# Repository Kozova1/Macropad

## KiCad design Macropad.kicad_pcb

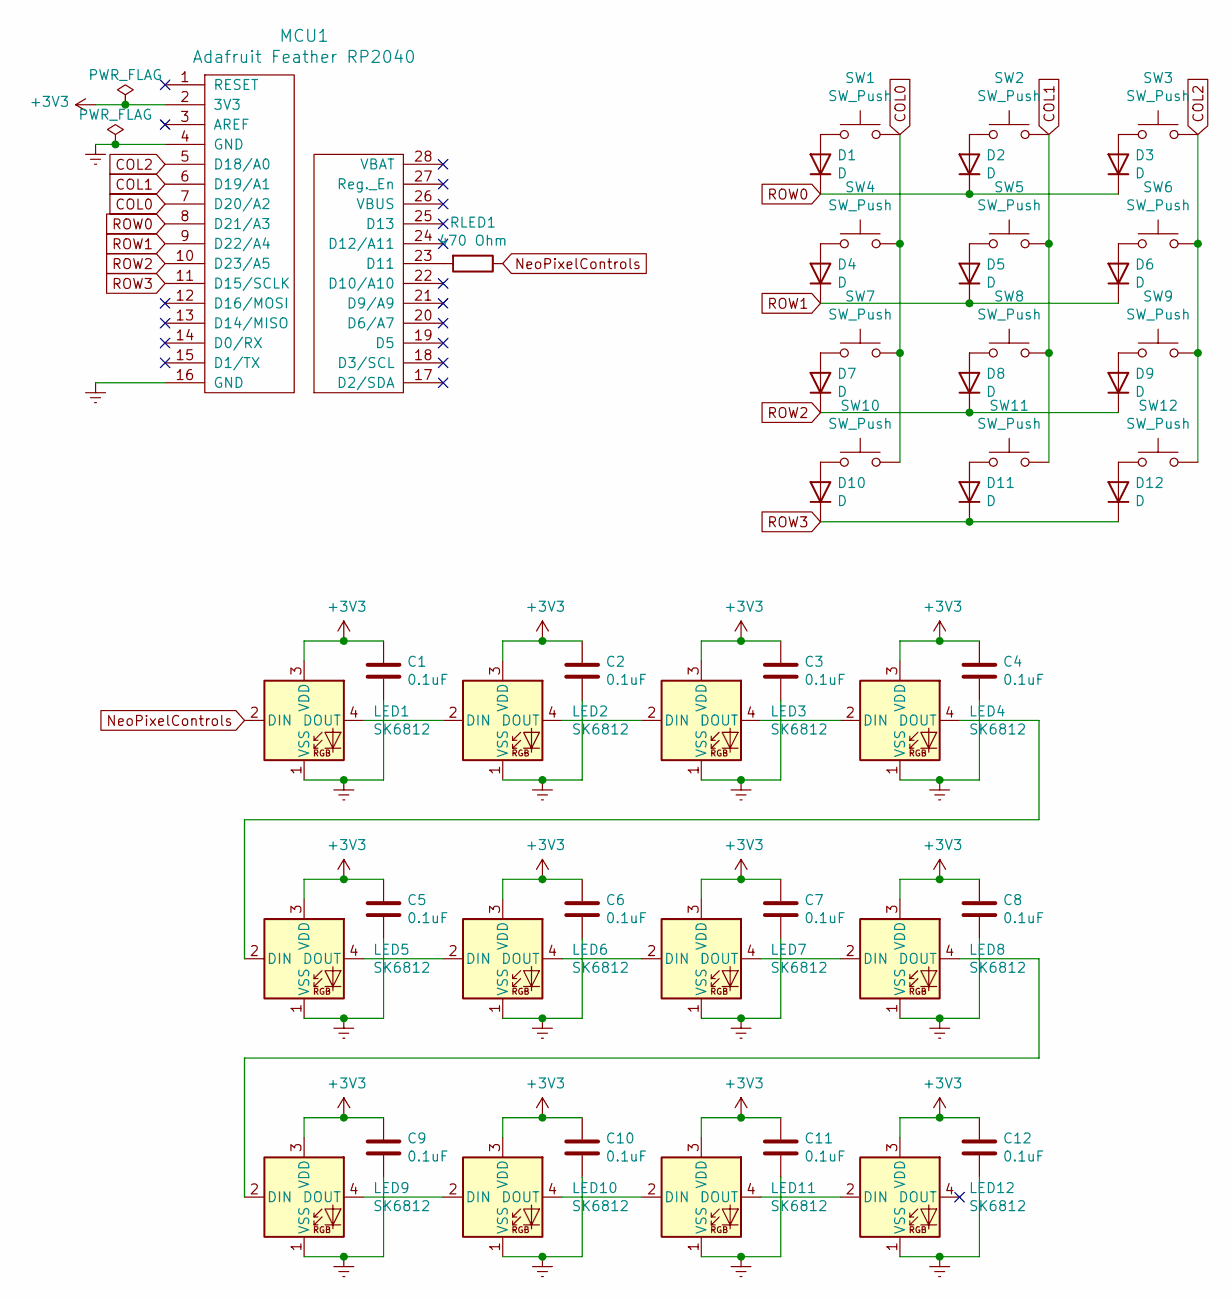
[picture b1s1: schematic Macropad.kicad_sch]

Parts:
C1, C2, C3, C4, C5, C6, C7, C8, C9, C10, C11, C12: 0.1uF; C_0805_2012Metric_Pad1.18x1.45mm_HandSolder
D1, D2, D3, D4, D5, D6, D7, D8, D9, D10, D11, D12: D; D_SOD-123
LED1, LED2, LED3, LED4, LED5, LED6, LED7, LED8, LED9, LED10, LED11, LED12: SK6812; MX_SK6812MINI-E
MCU1: Adafruit Feather RP2040; Adafruit_Feather_conn.kicad_mod
RLED1: 470 Ohm; R_Axial_DIN0207_L6.3mm_D2.5mm_P10.16mm_Horizontal
SW1, SW2, SW3, SW4, SW5, SW6, SW7, SW8, SW9, SW10, SW11, SW12: SW_Push; SW_Hotswap_Kailh_1.00u

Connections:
+3V3: C1.1, C2.1, C3.1, C4.1, C5.1, C6.1, C7.1, C8.1, C9.1, C10.1, C11.1, C12.1, LED1.3 (VDD), LED2.3 (VDD), LED3.3 (VDD), LED4.3 (VDD), LED5.3 (VDD), LED6.3 (VDD), LED7.3 (VDD), LED8.3 (VDD), LED9.3 (VDD), LED10.3 (VDD), LED11.3 (VDD), LED12.3 (VDD), MCU1.2 (3V3)
COL0: MCU1.7 (D20/A2), SW1.2, SW4.2, SW7.2, SW10.2
COL1: MCU1.6 (D19/A1), SW2.2, SW5.2, SW8.2, SW11.2
COL2: MCU1.5 (D18/A0), SW3.2, SW6.2, SW9.2, SW12.2
Earth: C1.2, C2.2, C3.2, C4.2, C5.2, C6.2, C7.2, C8.2, C9.2, C10.2, C11.2, C12.2, LED1.1 (VSS), LED2.1 (VSS), LED3.1 (VSS), LED4.1 (VSS), LED5.1 (VSS), LED6.1 (VSS), LED7.1 (VSS), LED8.1 (VSS), LED9.1 (VSS), LED10.1 (VSS), LED11.1 (VSS), LED12.1 (VSS), MCU1.4 (GND), MCU1.16 (GND)
NeoPixelControls: LED1.2 (DIN), RLED1.1
unnamed: D1.2 (A), SW1.1
unnamed: D2.2 (A), SW2.1
unnamed: D3.2 (A), SW3.1
unnamed: D4.2 (A), SW4.1
unnamed: D5.2 (A), SW5.1
unnamed: D6.2 (A), SW6.1
unnamed: D7.2 (A), SW7.1
unnamed: D8.2 (A), SW8.1
unnamed: D9.2 (A), SW9.1
unnamed: D10.2 (A), SW10.1
unnamed: D11.2 (A), SW11.1
unnamed: D12.2 (A), SW12.1
unnamed: LED1.4 (DOUT), LED2.2 (DIN)
unnamed: LED2.4 (DOUT), LED3.2 (DIN)
unnamed: LED3.4 (DOUT), LED4.2 (DIN)
unnamed: LED4.4 (DOUT), LED5.2 (DIN)
unnamed: LED5.4 (DOUT), LED6.2 (DIN)
unnamed: LED6.4 (DOUT), LED7.2 (DIN)
unnamed: LED7.4 (DOUT), LED8.2 (DIN)
unnamed: LED8.4 (DOUT), LED9.2 (DIN)
unnamed: LED9.4 (DOUT), LED10.2 (DIN)
unnamed: LED10.4 (DOUT), LED11.2 (DIN)
unnamed: LED11.4 (DOUT), LED12.2 (DIN)
unnamed: MCU1.23 (D11), RLED1.2
ROW0: D1.1 (K), D2.1 (K), D3.1 (K), MCU1.8 (D21/A3)
ROW1: D4.1 (K), D5.1 (K), D6.1 (K), MCU1.9 (D22/A4)
ROW2: D7.1 (K), D8.1 (K), D9.1 (K), MCU1.10 (D23/A5)
ROW3: D10.1 (K), D11.1 (K), D12.1 (K), MCU1.11 (D15/SCLK)

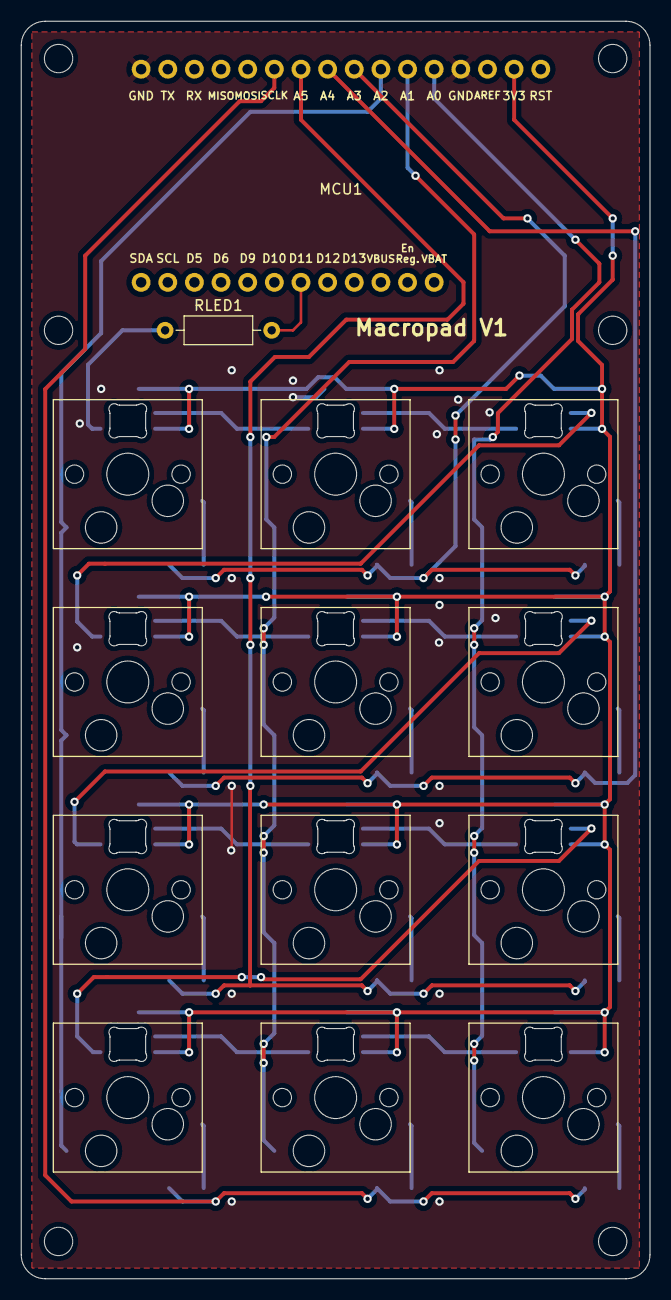
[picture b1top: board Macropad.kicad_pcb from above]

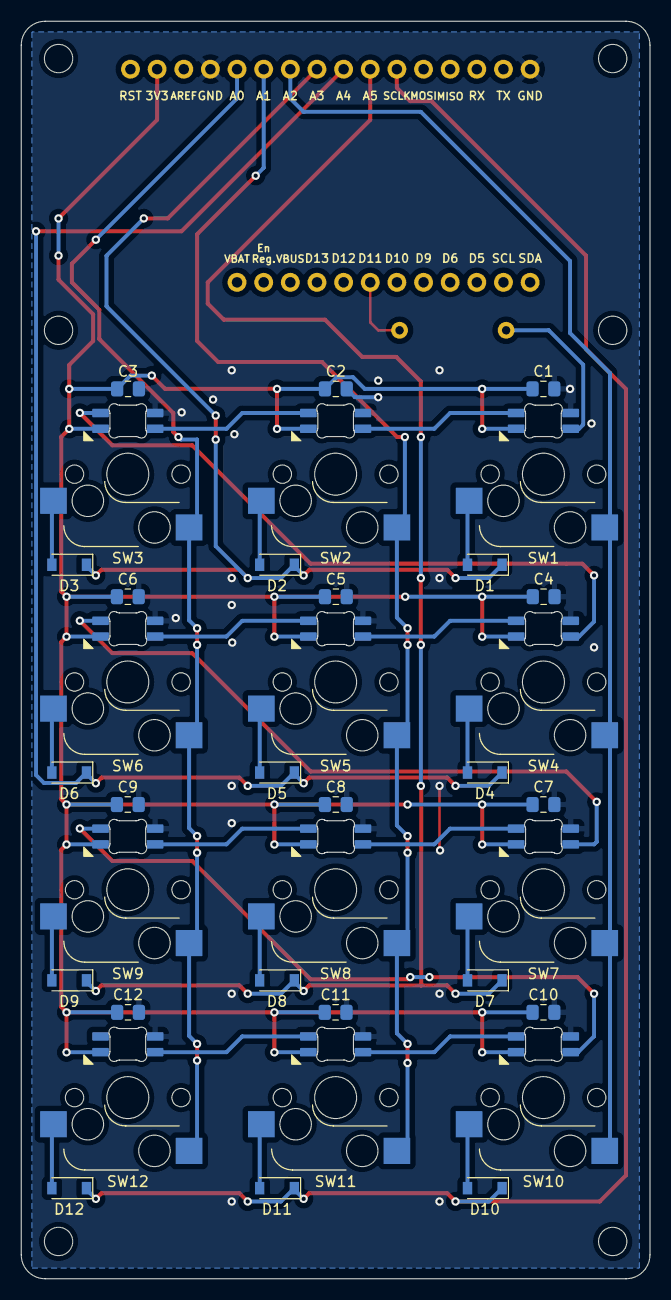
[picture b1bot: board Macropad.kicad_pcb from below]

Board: 2 copper layers, 59.9 x 119.9 mm, 50 parts (24 on the bottom side), 34 nets.

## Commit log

2021-08-29 Added silkscreen stuff
2021-08-30 updated label
2021-09-25 Final Version
2021-09-25 Added Case 3D Model
